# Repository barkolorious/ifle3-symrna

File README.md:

A computer based on Ben Eater's 6502 series.

The IC's were bought from Mouser and the PCB was manufactured by JLCPCB.
Here's the list of the IC's I used:
- **W65C02S6TPG-14**
  - MPU 8-bit Microprocessor
- **AS6C62256-55PCN**
  - SRAM 256K, 2.7-5.5V, 55ns 32K x 8 Asynch SRAM
- **AT28C256-15PU**
  - EEPROM 256K 32K x 8 150 ns 4.5V-5.5V
- **W65C22S6TPG-14**
  - Controller Interface IC Versatile Interface Adapter
- **W65C51N6TPG-14**
  - Specialised Asynch Communication Interface Adapter
- **MAX232EIN**
  - RS232 Line Driver/Receiver

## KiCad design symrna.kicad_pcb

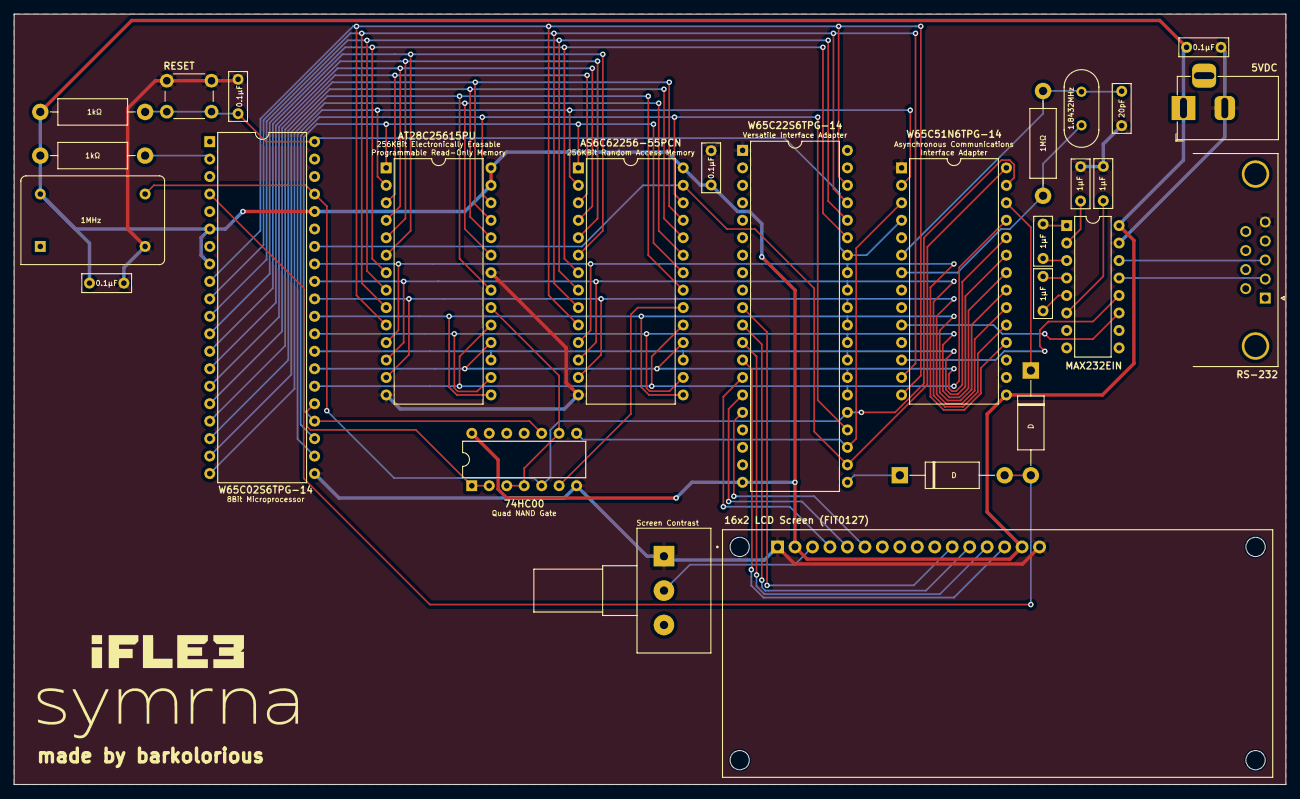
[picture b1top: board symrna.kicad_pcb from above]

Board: 2 copper layers, 184.9 x 112.0 mm, 28 parts (0 on the bottom side), 56 nets.

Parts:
C1: 20pF; C_Disc_D7.0mm_W2.5mm_P5.00mm
C2, C3, C4, C5: 1µF; C_Disc_D7.0mm_W2.5mm_P5.00mm
C6, C7, C8, C9: 0.1µF; C_Disc_D7.0mm_W2.5mm_P5.00mm
D25, D26: D; D_DO-15_P15.24mm_Horizontal
J1: DE9_Plug; DSUB-9_Female_Horizontal_P2.77x2.84mm_EdgePinOffset7.70mm_H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
J2: Jack-DC; BarrelJack_Horizontal
R25: 1MΩ; R_Axial_DIN0411_L9.9mm_D3.6mm_P15.24mm_Horizontal
R26, R27: 1kΩ; R_Axial_DIN0411_L9.9mm_D3.6mm_P15.24mm_Horizontal
RV1: R_Potentiometer; Potentiometer_Alps_RK163_Single_Horizontal
SW1: SW_Push; SW_PUSH_6mm_H7.3mm
U1: 28C256; DIP-28_W15.24mm
U2: HM62256BLP; DIP-28_W15.24mm
U3: MAX232; DIP-16_W7.62mm
U4: 74HC00; DIP-14_W7.62mm
U5: W65C02SxP; DIP-40_W15.24mm
U6: W65C22NxP; DIP-40_W15.24mm
U7: W65C51NxP; DIP-28_W15.24mm
U8: LCD-16X2; MODULE_LCD-16X2
X1: 1MHz; Oscillator_DIP-14
Y1: 1.8432MHz; Crystal_HC49-U_Vertical

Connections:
+5V: C7.1, C8.1, C9.1, J2.1, R26.1, R27.1, U1.27 (~WE), U1.28 (VCC), U2.28 (VCC), U3.16 (VCC), U4.14 (VCC), U5.6 (~NMI), U5.8 (VDD), U5.36 (BE), U6.20 (VCC), U7.15 (VCC), U8.2 (VDD), U8.15 (A), X1.14 (Vcc)
/a0: U1.10 (A0), U2.10 (A0), U5.9 (A0), U6.38 (RS0), U7.14 (RS1)
/a1: U1.9 (A1), U2.9 (A1), U5.10 (A1), U6.37 (RS1), U7.13 (RS0)
/a2: U1.8 (A2), U2.8 (A2), U5.11 (A2), U6.36 (RS2)
/a3: U1.7 (A3), U2.7 (A3), U5.12 (A3), U6.35 (RS3)
/a4: U1.6 (A4), U2.6 (A4), U5.13 (A4)
/a5: U1.5 (A5), U2.5 (A5), U5.14 (A5)
/a6: U1.4 (A6), U2.4 (A6), U5.15 (A6)
/a7: U1.3 (A7), U2.3 (A7), U5.16 (A7)
/a8: U1.25 (A8), U2.25 (A8), U5.17 (A8)
/a9: U1.24 (A9), U2.24 (A9), U5.18 (A9)
/a10: U1.21 (A10), U2.21 (A10), U5.19 (A10)
/a11: U1.23 (A11), U2.23 (A11), U5.20 (A11)
/a12: U1.2 (A12), U2.2 (A12), U5.22 (A12), U7.2 (CS1)
/a13: U1.26 (A13), U2.26 (A13), U5.23 (A13), U6.24 (CS1)
/a14: U1.1 (A14), U2.1 (A14), U2.22 (~OE), U4.10, U5.24 (A14)
/a15: U4.1, U4.2, U5.25 (A15)
/d0: U1.11 (D0), U2.11 (Q0), U5.33 (D0), U6.33 (D0), U7.18 (D0)
/d1: U1.12 (D1), U2.12 (Q1), U5.32 (D1), U6.32 (D1), U7.19 (D1)
/d2: U1.13 (D2), U2.13 (Q2), U5.31 (D2), U6.31 (D2), U7.20 (D2)
/d3: U1.15 (D3), U2.15 (Q3), U5.30 (D3), U6.30 (D3), U7.21 (D3)
/d4: U1.16 (D4), U2.16 (Q4), U5.29 (D4), U6.29 (D4), U7.22 (D4)
/d5: U1.17 (D5), U2.17 (Q5), U5.28 (D5), U6.28 (D5), U7.23 (D5)
/d6: U1.18 (D6), U2.18 (Q6), U5.27 (D6), U6.27 (D6), U7.24 (D6)
/d7: U1.19 (D7), U2.19 (Q7), U5.26 (D7), U6.26 (D7), U7.25 (D7)
GND: C1.2, C4.2, C5.2, C6.2, C7.2, C8.2, C9.2, J1.5, J2.2, RV1.1, SW1.1, U1.14 (GND), U1.22 (~OE), U2.14 (GND), U3.15 (GND), U4.7 (GND), U5.21 (VSS), U6.1 (VSS), U7.1 (VSS), U8.1 (VSS), U8.16 (K), X1.7 (GND)
unnamed: D25.2 (A), D26.2 (A), U5.4 (~IRQ)
unnamed: D25.1 (K), U6.21 (~IRQ)
unnamed: D26.1 (K), U7.26 (~IRQ)
unnamed: U1.20 (~CS), U4.3, U4.4, U4.9
unnamed: U2.20 (~CS), U4.6
unnamed: U2.27 (~WE), U5.34 (R/~W), U6.22 (R/~W), U7.28 (R/~W)
unnamed: C2.1, U3.1 (C1+)
unnamed: C2.2, U3.3 (C1-)
unnamed: C3.1, U3.4 (C2+)
unnamed: C3.2, U3.5 (C2-)
unnamed: J1.2, U3.13 (R1IN)
unnamed: U3.12 (R1OUT), U7.12 (RxD)
unnamed: U3.11 (T1IN), U7.10 (TxD)
unnamed: J1.3, U3.14 (T1OUT)
unnamed: C4.1, U3.2 (VS+)
unnamed: C5.1, U3.6 (VS-)
unnamed: R26.2, U5.2 (RDY)
unnamed: C6.1, R27.2, SW1.2, U5.40 (~RES), U6.34 (~RES), U7.4 (~RES)
unnamed: U4.5, U5.37 (ϕ0), U6.25 (ϕ2), U7.27 (ϕ2), X1.8 (OUT)
unnamed: U6.10 (PB0), U8.11 (DB4)
unnamed: U6.11 (PB1), U8.12 (DB5)
unnamed: U6.12 (PB2), U8.13 (DB6)
unnamed: U6.13 (PB3), U8.14 (DB7)
unnamed: U6.14 (PB4), U8.4 (RS)
unnamed: U6.15 (PB5), U8.5 (R/W)
unnamed: U6.16 (PB6), U8.6 (E)
unnamed: U4.8, U6.23 (~CS2), U7.3 (~CS2)
unnamed: C1.1, R25.1, U7.6 (XTAL1), Y1.2
unnamed: R25.2, U7.7 (XTAL2), Y1.1
unnamed: RV1.2, U8.3 (VO)

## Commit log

2024-08-14 Rename text053.png to logo.png
